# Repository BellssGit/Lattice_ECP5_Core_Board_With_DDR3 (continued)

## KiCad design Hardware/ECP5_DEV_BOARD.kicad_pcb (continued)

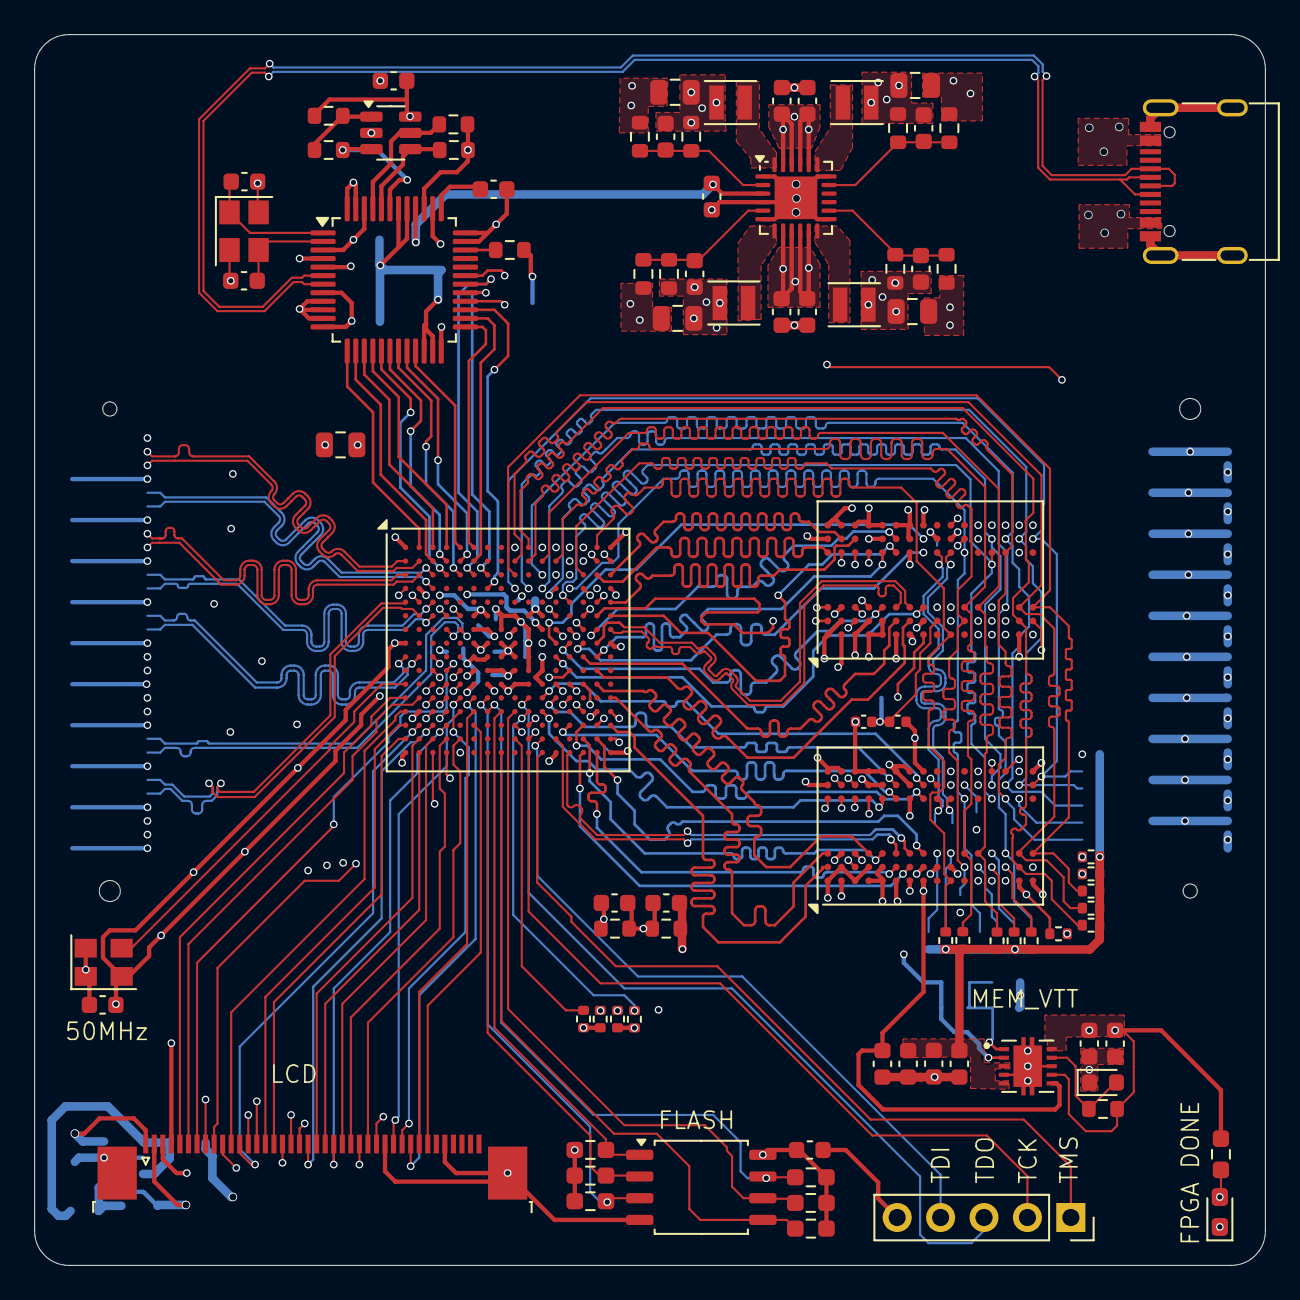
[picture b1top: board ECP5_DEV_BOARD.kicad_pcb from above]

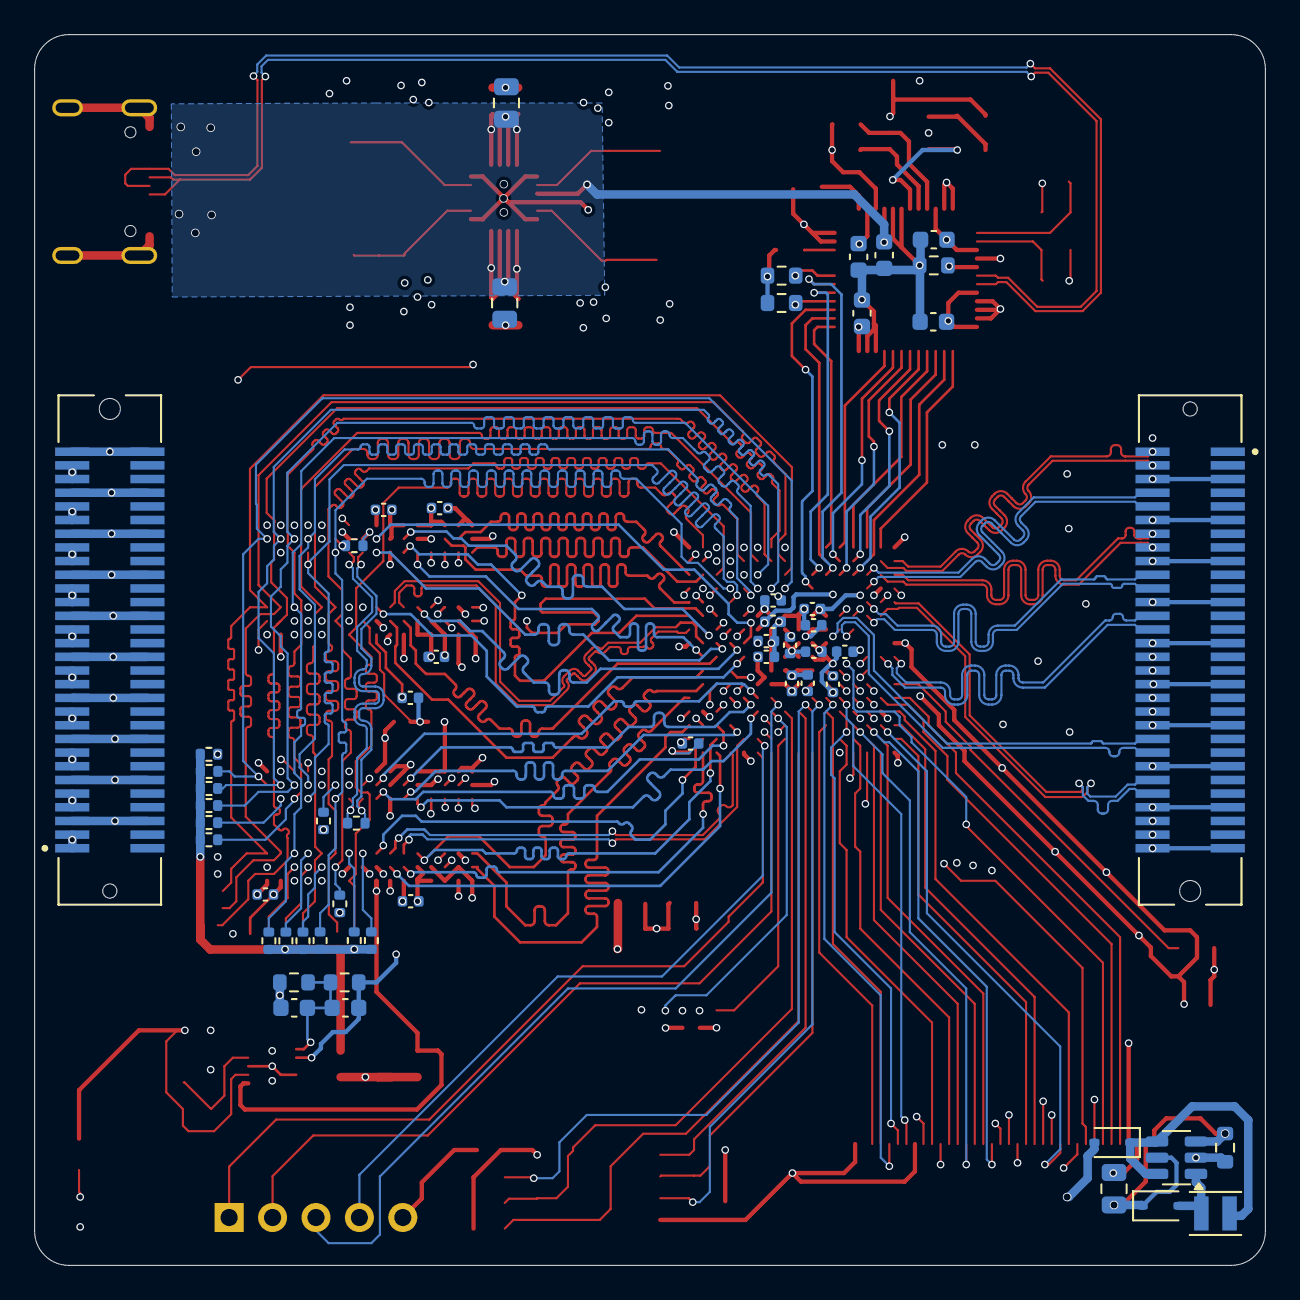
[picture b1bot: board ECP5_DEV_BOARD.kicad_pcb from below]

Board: 6 copper layers, 72.0 x 72.0 mm, 144 parts (57 on the bottom side), 189 nets.

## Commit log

2025-01-26 Upload hardware and test project
2025-01-26 fix README.md because I am a dumpass
